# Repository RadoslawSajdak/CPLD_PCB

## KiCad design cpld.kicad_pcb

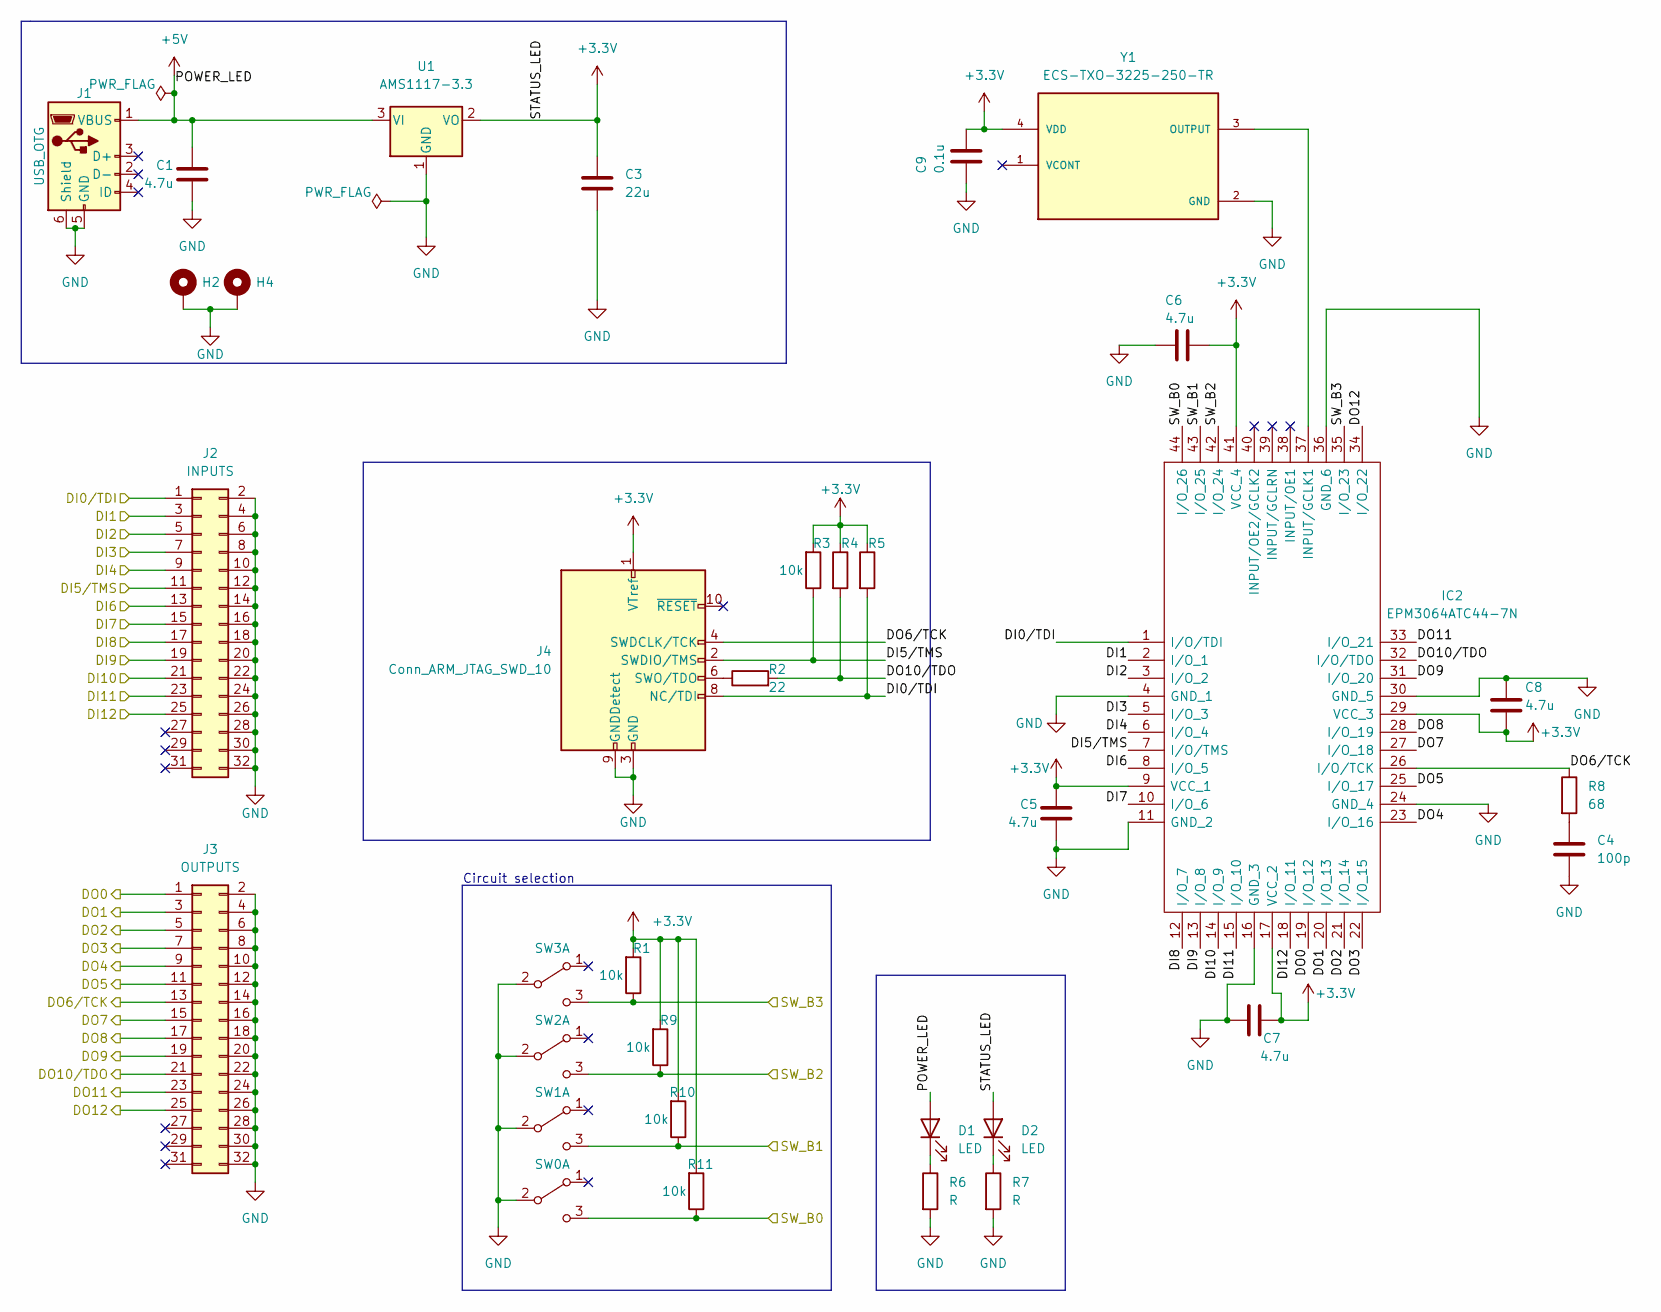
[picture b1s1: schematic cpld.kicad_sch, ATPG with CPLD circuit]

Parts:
C1, C5, C6, C7, C8: 4.7u; C_0603_1608Metric
C3: 22u; C_0603_1608Metric
C4: 100p; C_0603_1608Metric
C9: 0.1u; C_0603_1608Metric
D1, D2: LED; LED_D3.0mm
H2, H4: MountingHole_Pad; MountingHole_3.2mm_M3_DIN965_Pad_TopBottom
IC2: EPM3064ATC44-7N; QFP80P1200X1200X120-44N; Manufacturer_Part_Number EPM3064ATC44-7N; Mouser Part Number 989-EPM3064ATC44-7N
J1: USB_OTG; USB_Micro-B_Amphenol_10118194_Horizontal
J2: INPUTS; PinSocket_2x16_P2.54mm_Vertical
J3: OUTPUTS; PinSocket_2x16_P2.54mm_Vertical
J4: Conn_ARM_JTAG_SWD_10; PinSocket_2x05_P2.54mm_Vertical_SMD
R1, R3, R4, R5, R9, R10, R11: 10k; R_0603_1608Metric
R2: 22; R_0603_1608Metric
R6, R7: R; R_0603_1608Metric
R8: 68; R_0603_1608Metric
SW0, SW1, SW2, SW3: SW_DPDT_x2; SW_E-Switch_EG1271_DPDT
U1: AMS1117-3.3; SOT-223-3_TabPin2
Y1: ECS-TXO-3225-250-TR; OSC_ECS-TXO-3225-250-TR; PARTREV N/A

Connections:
+3.3V: C3.1, C5.2, C6.2, C7.1, C8.2, C9.2, D2.2 (A), IC2.9 (VCC_1), IC2.17 (VCC_2), IC2.29 (VCC_3), IC2.41 (VCC_4), J4.1 (VTref), R1.2, R3.2, R4.1, R5.1, R9.2, R10.2, R11.2, U1.2 (VO), Y1.4 (VDD)
+5V: C1.2, D1.2 (A), J1.1 (VBUS), U1.3 (VI)
/DI0/TDI: IC2.1 (I/O/TDI), J2.1, J4.8 (NC/TDI), R5.2
/DI1: IC2.2 (I/O_1), J2.3
/DI2: IC2.3 (I/O_2), J2.5
/DI3: IC2.5 (I/O_3), J2.7
/DI4: IC2.6 (I/O_4), J2.9
/DI5/TMS: IC2.7 (I/O/TMS), J2.11, J4.2 (SWDIO/TMS), R3.1
/DI6: IC2.8 (I/O_5), J2.13
/DI7: IC2.10 (I/O_6), J2.15
/DI8: IC2.12 (I/O_7), J2.17
/DI9: IC2.13 (I/O_8), J2.19
/DI10: IC2.14 (I/O_9), J2.21
/DI11: IC2.15 (I/O_10), J2.23
/DI12: IC2.18 (I/O_11), J2.25
/DO0: IC2.19 (I/O_12), J3.1
/DO1: IC2.20 (I/O_13), J3.3
/DO2: IC2.21 (I/O_14), J3.5
/DO3: IC2.22 (I/O_15), J3.7
/DO4: IC2.23 (I/O_16), J3.9
/DO5: IC2.25 (I/O_17), J3.11
/DO6/TCK: IC2.26 (I/O/TCK), J3.13, J4.4 (SWDCLK/TCK), R8.1
/DO7: IC2.27 (I/O_18), J3.15
/DO8: IC2.28 (I/O_19), J3.17
/DO9: IC2.31 (I/O_20), J3.19
/DO10/TDO: IC2.32 (I/O/TDO), J3.21, R2.2, R4.2
/DO11: IC2.33 (I/O_21), J3.23
/DO12: IC2.34 (I/O_22), J3.25
/SW_B0: IC2.44 (I/O_26), R11.1, SW0.3 (C)
/SW_B1: IC2.43 (I/O_25), R10.1, SW1.3 (C)
/SW_B2: IC2.42 (I/O_24), R9.1, SW2.3 (C)
/SW_B3: IC2.35 (I/O_23), R1.1, SW3.3 (C)
GND: C1.1, C3.2, C4.2, C5.1, C6.1, C7.2, C8.1, C9.1, H2.1, H4.1, IC2.4 (GND_1), IC2.11 (GND_2), IC2.16 (GND_3), IC2.24 (GND_4), IC2.30 (GND_5), IC2.36 (GND_6), J1.5 (GND), J1.6 (Shield), J2.2, J2.4, J2.6, J2.8, J2.10, J2.12, J2.14, J2.16, J2.18, J2.20, J2.22, J2.24, J2.26, J2.28, J2.30, J2.32, J3.2, J3.4, J3.6, J3.8, J3.10, J3.12, J3.14, J3.16, J3.18, J3.20, J3.22, J3.24, J3.26, J3.28, J3.30, J3.32, J4.3 (GND), J4.5 (GND), J4.9 (GNDDetect), R6.2, R7.2, SW0.2 (B), SW1.2 (B), SW2.2 (B), SW3.2 (B), U1.1 (GND), Y1.2 (GND)
unnamed: C4.1, R8.2
unnamed: D1.1 (K), R6.1
unnamed: D2.1 (K), R7.1
unnamed: IC2.37 (INPUT/GCLK1), Y1.3 (OUTPUT)
unnamed: J4.6 (SWO/TDO), R2.1

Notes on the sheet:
Circuit selection

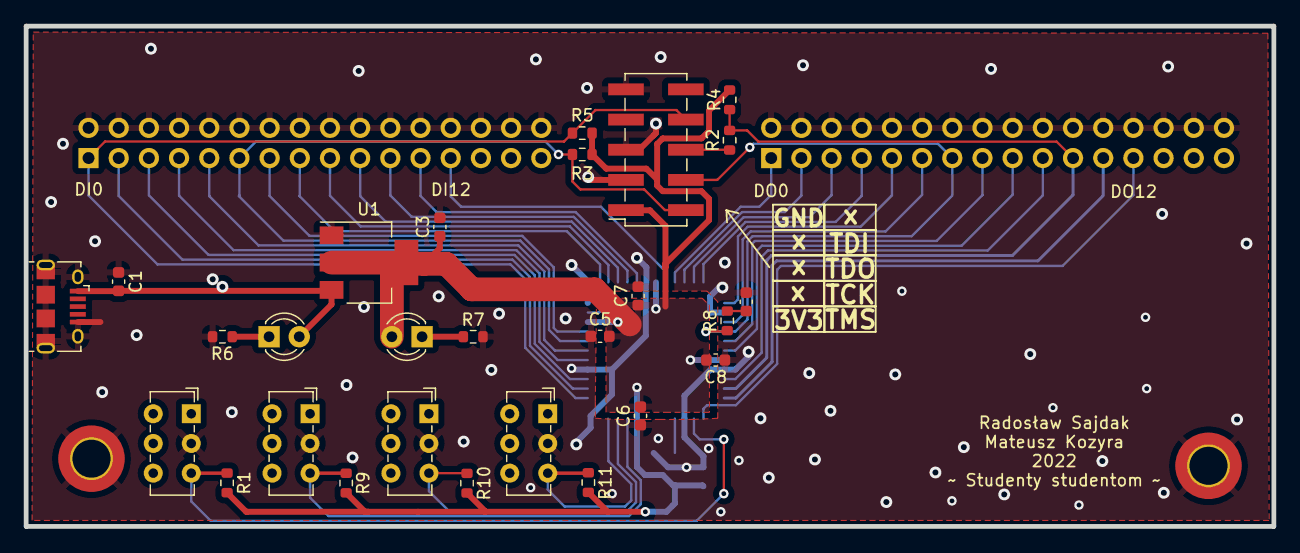
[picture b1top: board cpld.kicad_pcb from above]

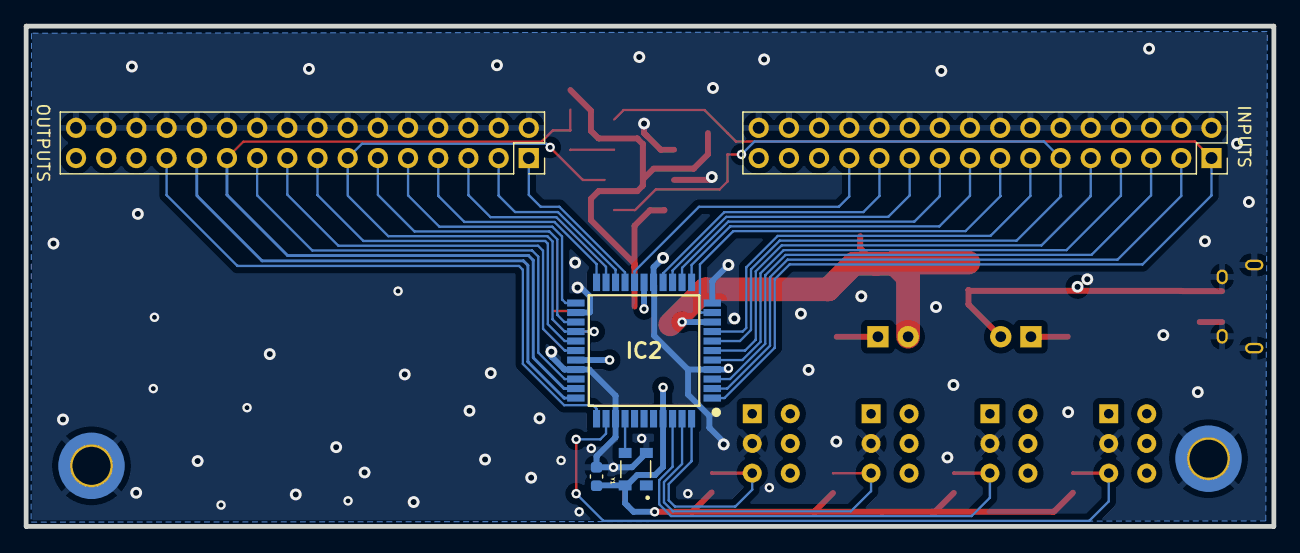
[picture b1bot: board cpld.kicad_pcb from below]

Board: 2 copper layers, 105.0 x 42.1 mm, 34 parts (5 on the bottom side), 38 nets.

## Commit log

2022-08-07 First version of the schematics
2022-08-07 Added revision and title
2022-08-18 Final PCB
2022-08-19 Improved PCB layout
2022-08-21 Changed connectors and LDO
2022-08-21 sent to the jlcpcb
2022-08-30 Ordered version
2022-08-30 Updated schematics pdf
2022-09-06 added pullups for the switches
2022-09-06 Studenty studentom
